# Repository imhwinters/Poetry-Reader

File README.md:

# Poetry-Reader
I made this project for my dad's birthday -- he loves reading poetry, but doesn't want to lug around heavy poetry books. I built this pocket-sized poetry reader to solve that problem.

## Demo (videos + images)

https://github.com/user-attachments/assets/ed4d790f-b5af-4959-8c8f-0a64da99f5de

https://github.com/user-attachments/assets/21cbcda3-095a-4b04-85aa-d2876527afe0

## Files
On this repo the code is a Platformio project, including the data sent via LittleFS to the Poetry Reader. The Schematic and PCB are in a Kicad project, which you can preview [here](https://kicanvas.org/?repo=https%3A%2F%2Fgithub.com%2Fimhwinters%2FPoetry-Reader%2Ftree%2Fmain%2FPCB%2520And%2520Schematic). 
The PCB isn't totally accurate -- due to manufacturing time/expenses I ended up just soldering this project on perfboard. The different layout meant that I ended up using different MCU pins for buttons based on convenience.

## BOM
|Part|Count|
|----|-----:|
|Xiao seeed esp32c3|1|
|Tactile buttons|6|
|22 guage wire (solid-core or threaded works, but I used solid-core)|idk|
|1.5" OLED IIC Screen|1|
|[3d Printed Case](https://cad.onshape.com/documents/d6cbfe09ed0ba8b33bb9ea9c/w/6fbf33e595bea7372ae94027/e/cdf8b9d88ac8b494c49c5fa8)|1|

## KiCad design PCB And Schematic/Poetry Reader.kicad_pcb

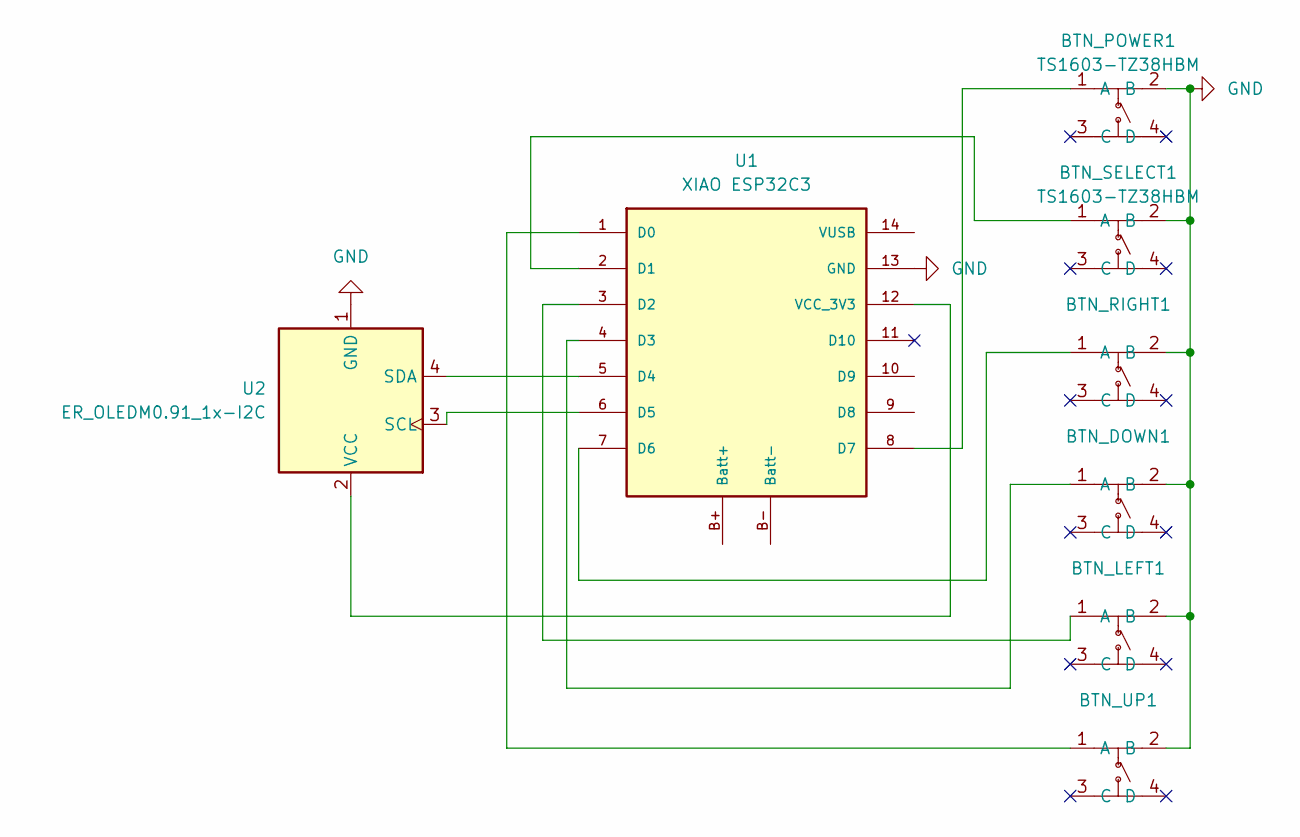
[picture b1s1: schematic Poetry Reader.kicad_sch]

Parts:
BTN_DOWN1: TS1603-TZ38HBM; SW-SMD_4P-L4.5-W4.5-P3.00-LS6.8; MPN TS1603-TZ38HBM; LCSC Part C36938886
BTN_LEFT1: TS1603-TZ38HBM; SW-SMD_4P-L4.5-W4.5-P3.00-LS6.8; MPN TS1603-TZ38HBM; LCSC Part C36938886
BTN_POWER1: TS1603-TZ38HBM; SW-SMD_4P-L4.5-W4.5-P3.00-LS6.8; MPN TS1603-TZ38HBM; LCSC Part C36938886
BTN_RIGHT1: TS1603-TZ38HBM; SW-SMD_4P-L4.5-W4.5-P3.00-LS6.8; MPN TS1603-TZ38HBM; LCSC Part C36938886
BTN_SELECT1: TS1603-TZ38HBM; SW-SMD_4P-L4.5-W4.5-P3.00-LS6.8; MPN TS1603-TZ38HBM; LCSC Part C36938886
BTN_UP1: TS1603-TZ38HBM; SW-SMD_4P-L4.5-W4.5-P3.00-LS6.8; MPN TS1603-TZ38HBM; LCSC Part C36938886
U1: XIAO ESP32C3; XIAO-ESP32-C3-DIP
U2: ER_OLEDM0.91_1x-I2C; 1.5_inch_IIC_OLED

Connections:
GND: BTN_DOWN1.2 (B), BTN_LEFT1.2 (B), BTN_POWER1.2 (B), BTN_RIGHT1.2 (B), BTN_SELECT1.2 (B), BTN_UP1.2 (B), U1.13 (GND), U2.1 (GND)
unnamed: BTN_DOWN1.1 (A), U1.4 (D3)
unnamed: BTN_LEFT1.1 (A), U1.3 (D2)
unnamed: BTN_POWER1.1 (A), U1.8 (D7)
unnamed: BTN_RIGHT1.1 (A), U1.7 (D6)
unnamed: BTN_SELECT1.1 (A), U1.2 (D1)
unnamed: BTN_UP1.1 (A), U1.1 (D0)
unnamed: U1.5 (D4), U2.4 (SDA)
unnamed: U1.6 (D5), U2.3 (SCL)
unnamed: U1.12 (VCC_3V3), U2.2 (VCC)

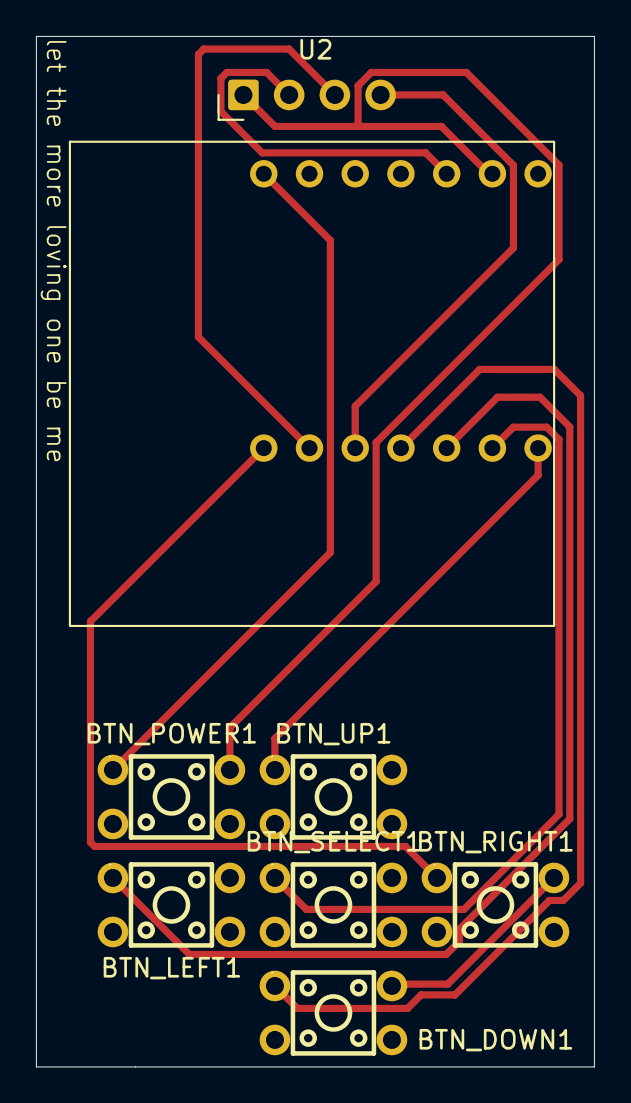
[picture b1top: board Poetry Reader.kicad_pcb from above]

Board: 2 copper layers, 31.0 x 57.2 mm, 8 parts (1 on the bottom side), 10 nets.

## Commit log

2026-06-14 Add code, PCB + schematic files
2026-06-14 Write README
2026-06-15 Reorder README
